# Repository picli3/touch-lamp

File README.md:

# Touch Lamp — Lámpara Vintage con Sensor Táctil

PCB con 3 LEDs que simulan ser filamento incandescente, diseñada para integrarse en una **lámpara vintage**. El control táctil está basado en el circuito integrado **SGL8022W**, que permite encendido/apagado y regulación de intensidad luminosa (dimmer) con solo tocar el electrodo sensor.

## Características

- **Control táctil** basado en SGL8022W (SOP-8)
- **3 LEDs** dispuestos para simular un filamento incandescente vintage
- **Regulación de intensidad** — toques repetidos cambian el brillo (ciclo: apagado → bajo → medio → alto → apagado)
- **Alimentación:** 5 VCC
- **Formato compacto** ideal para montaje dentro de lámparas decorativas
- Diseñado en **KiCad 10.0**

## Componentes Principales

| Ref | Componente | Descripción | Footprint |
|-----|-----------|-------------|-----------|
| U1 | **SGL8022W** | IC touch sensor para regulación de brillo LED | SOP-8 |
| Q1 | NPN transistor | Driver de salida para LEDs | SOT-23-3 |
| D1-D3 | LED 0603 | LEDs simulando filamento incandescente | 0603 LED |
| C1 | 100 nF | Capacitor de desacople | 0603 |
| C2 | 10 µF | Capacitor de filtro de alimentación | 0805 |
| C3 | 10 nF | Capacitor de oscilación del SGL8022W | 0603 |
| R1 | 4.7 kΩ | Resistencia de polarización | 0603 |
| R2 | 1 kΩ | Resistencia de base del transistor | 0603 |
| R3 | 5.1 Ω | Resistencia limitadora de corriente de LEDs | 0603 |
| R4, R5 | 5.1 kΩ | Resistencias de configuración de modo | 0603 |

## Cómo Funciona

1. **Sensor táctil:** El SGL8022W detecta la capacitancia del cuerpo humano a través de un electrodo conectado al pin TI (Touch Input, pin 5).
2. **Procesamiento:** El chip interpreta los toques y controla la salida PWM en el pin SO (pin 7).
3. **Driver de salida:** La señal PWM pasa por un transistor NPN (Q1) que maneja los 3 LEDs en paralelo.
4. **Modos de operación:** Configurables mediante los pines OPT1/OPT2 y los jumpers JP1/JP2 en la PCB.

### Ciclo de operación por defecto

| Toque | Estado |
|-------|--------|
| 1er toque | Encendido — brillo bajo |
| 2do toque | Brillo medio |
| 3er toque | Brillo alto |
| 4to toque | Apagado |

## Archivos del Proyecto

| Archivo | Descripción |
|---------|-------------|
| `lampara_bintge.kicad_sch` | Esquemático en KiCad |
| `lampara_bintge.kicad_pcb` | Diseño de PCB en KiCad |
| `lampara_bintge.kicad_pro` | Proyecto KiCad |
| `lampara_bintge.kicad_prl` | Archivo de diseño de placa |

## BOM (Bill of Materials)

El archivo `BOM.csv` incluido en los releases contiene la lista completa de materiales con referencias, valores, footprints y descripciones.

## Licencia

Este proyecto se comparte con fines educativos y de hobby. Si lo usas o modificas, agradeceremos la atribución.

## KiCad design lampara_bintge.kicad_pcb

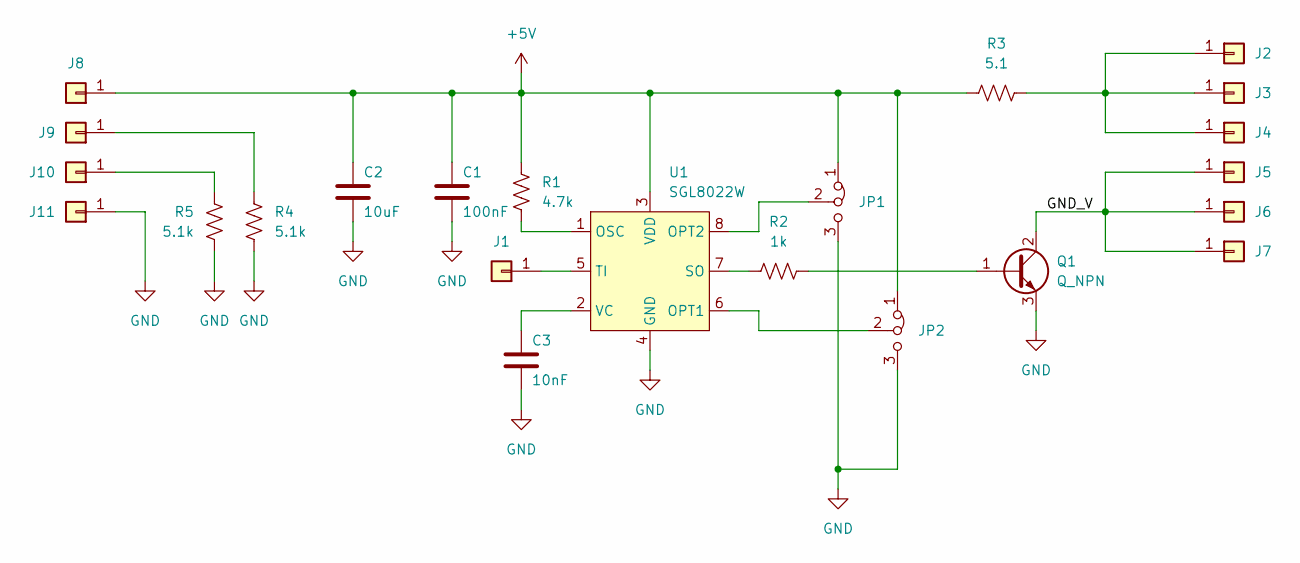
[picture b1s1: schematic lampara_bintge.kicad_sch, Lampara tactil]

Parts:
C1: 100nF; C_0603_1608Metric
C2: 10uF; C_0805_2012Metric
C3: 10nF; C_0603_1608Metric
J1: Conn_01x01; TestPoint_Pad_2.5x2.5mm
J2, J3, J4, J5, J6, J7: Conn_01x01; TestPoint_THTPad_2.5x2.5mm_Drill1.2mm
J8, J9, J10, J11: Conn_01x01; TestPoint_Pad_1.5x1.5mm
JP1, JP2: Jumper_3_Bridged12; SolderJumper-3_P1.3mm_Bridged12_RoundedPad1.0x1.5mm
Q1: Q_NPN; SOT-23-3
R1: 4.7k; R_0603_1608Metric
R2: 1k; R_0603_1608Metric
R3: 5.1; R_0603_1608Metric
R4, R5: 5.1k; R_0603_1608Metric
U1: SGL8022W; SOP-8_3.76x4.96mm_P1.27mm

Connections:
+5V: C1.1, C2.1, J8.1 (Pin_1_1), JP1.1 (A), JP2.1 (A), R1.2, R3.2, U1.3 (VDD)
/GND_V: J5.1 (Pin_1_1), J6.1 (Pin_1_1), J7.1 (Pin_1_1), Q1.2 (C)
GND: C1.2, C2.2, C3.2, J11.1 (Pin_1_1), JP1.3 (B), JP2.3 (B), Q1.3 (E), R4.1, R5.1, U1.4 (GND)
unnamed: J1.1 (Pin_1_1), U1.5 (TI)
unnamed: J2.1 (Pin_1_1), J3.1 (Pin_1_1), J4.1 (Pin_1_1), R3.1
unnamed: J9.1 (Pin_1_1), R4.2
unnamed: J10.1 (Pin_1_1), R5.2
unnamed: JP1.2 (C), U1.8 (OPT2)
unnamed: JP2.2 (C), U1.6 (OPT1)
unnamed: Q1.1 (B), R2.1
unnamed: R1.1, U1.1 (OSC)
unnamed: R2.2, U1.7 (SO)
unnamed: C3.1, U1.2 (VC)

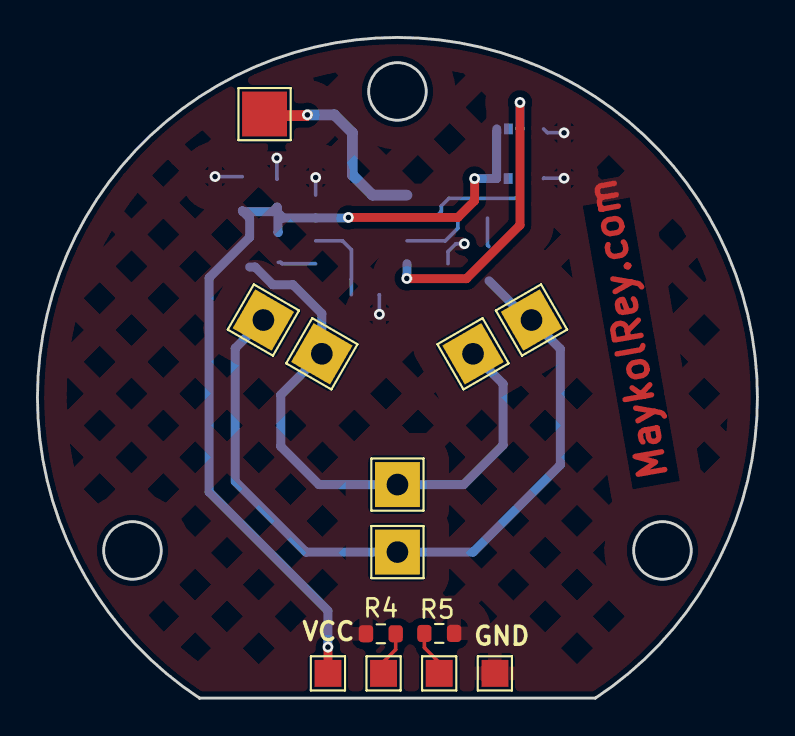
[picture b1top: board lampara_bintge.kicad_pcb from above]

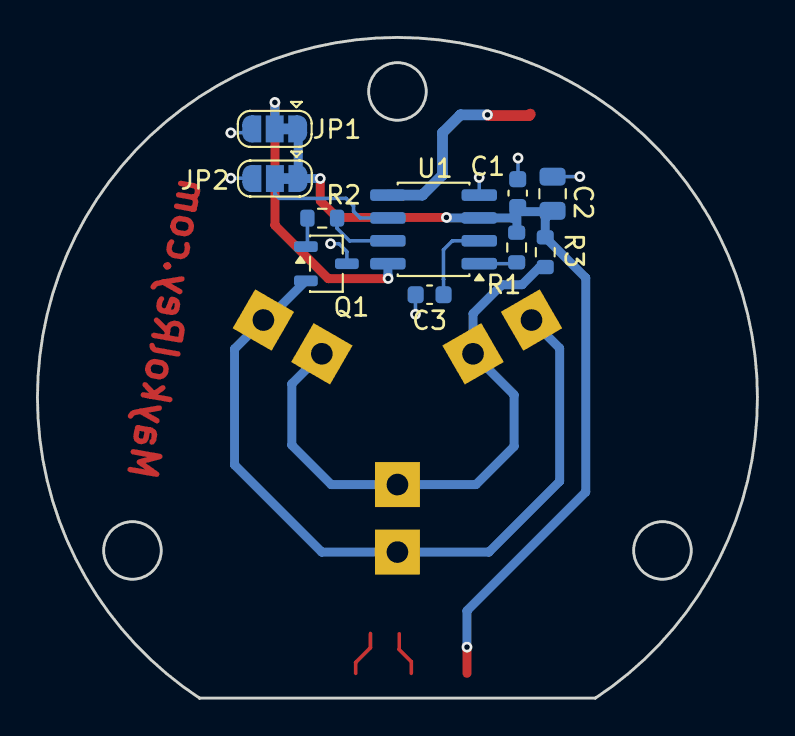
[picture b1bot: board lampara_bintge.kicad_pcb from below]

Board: 2 copper layers, 40.0 x 36.7 mm, 23 parts (10 on the bottom side), 13 nets.

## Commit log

2026-05-16 agregando sensor tactil
2026-05-17 docs: add README and board images for v1.0.0
    - README.md with full project description, BOM, and usage
    - Top and bottom PCB views in docs/
